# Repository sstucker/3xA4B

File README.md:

# 3xA4B
Utility PCB board. DC summing amplifier. Channels A are divided by 4 and optionally routed through a basic passive filter before being added to Channels B.

Three channels. BNC inputs and outputs. DIN-6 input for +12/-12 DC in. 

Schematic and board available in EAGLE formats. Some parts will need to be substituted. CAM data archive provided as well.

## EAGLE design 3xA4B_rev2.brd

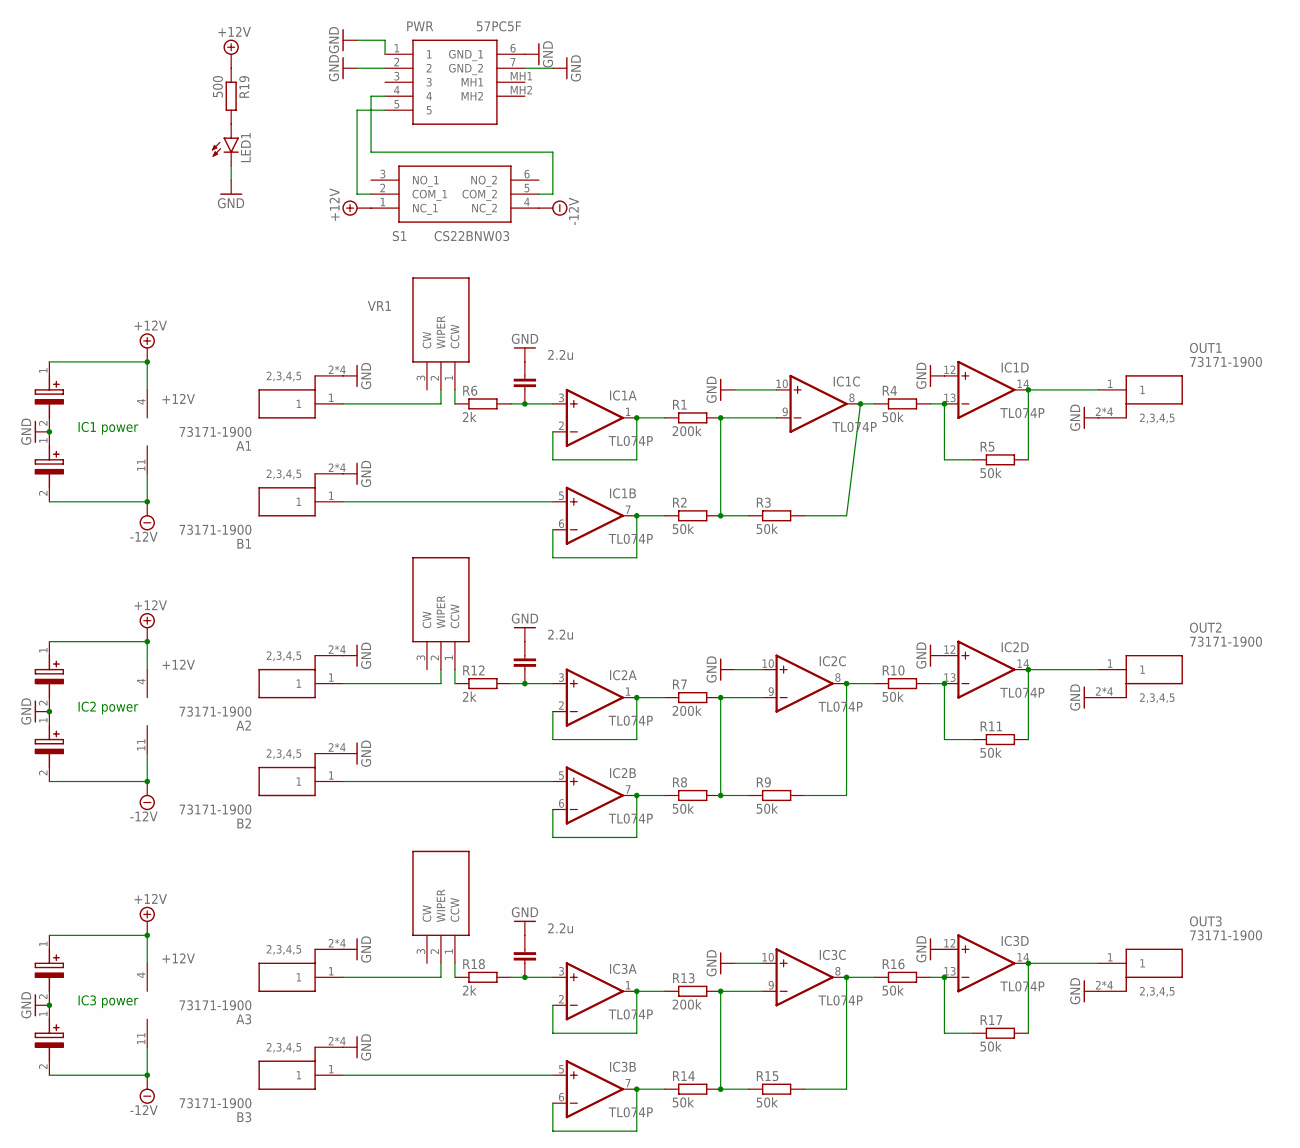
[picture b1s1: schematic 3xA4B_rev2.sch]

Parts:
A1, A2, A3: 73171-1900
B1, B2, B3: 73171-1900
C1, C2, C3, C4, C5, C6: TAP225K050GSB
IC1, IC2, IC3: TL074P; DIL14
LED1: LED3MM
OUT1, OUT2, OUT3: 73171-1900
PWR: 57PC5F; MPN 57PC5F
R1, R7, R13: 200k; 0207/10
R2, R3, R4, R5, R8, R9, R10, R11, R14, R15, R16, R17: 50k; 0207/10
R6, R12, R18: 2k; 0207/10
R19: 500; 0207/10
S1: CS22BNW03; MPN CS22BNW03
VC1, VC2, VC3: 2.2u; C025-024X044
VR1, VR2, VR3: 3299W-1-104LF; 3299W-1-104LF_1; MPN 3299W-1-104LF

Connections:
+12V: C1.1 (+), C3.1 (+), C5.1 (+), IC1.4 (V+), IC2.4 (V+), IC3.4 (V+), R19.1, S1.1 (NC_1)
-12V: C2.2 (-), C4.2 (-), C6.2 (-), IC1.11 (V-), IC2.11 (V-), IC3.11 (V-), S1.4 (NC_2)
GND: A1.2 (2,3,4,5), A1.3 (2,3,4,5), A1.4 (2,3,4,5), A1.5 (2,3,4,5), A2.2 (2,3,4,5), A2.3 (2,3,4,5), A2.4 (2,3,4,5), A2.5 (2,3,4,5), A3.2 (2,3,4,5), A3.3 (2,3,4,5), A3.4 (2,3,4,5), A3.5 (2,3,4,5), B1.2 (2,3,4,5), B1.3 (2,3,4,5), B1.4 (2,3,4,5), B1.5 (2,3,4,5), B2.2 (2,3,4,5), B2.3 (2,3,4,5), B2.4 (2,3,4,5), B2.5 (2,3,4,5), B3.2 (2,3,4,5), B3.3 (2,3,4,5), B3.4 (2,3,4,5), B3.5 (2,3,4,5), C1.2 (-), C2.1 (+), C3.2 (-), C4.1 (+), C5.2 (-), C6.1 (+), IC1.10 (+IN), IC1.12 (+IN), IC2.10 (+IN), IC2.12 (+IN), IC3.10 (+IN), IC3.12 (+IN), LED1.K (C), OUT1.2 (2,3,4,5), OUT1.3 (2,3,4,5), OUT1.4 (2,3,4,5), OUT1.5 (2,3,4,5), OUT2.2 (2,3,4,5), OUT2.3 (2,3,4,5), OUT2.4 (2,3,4,5), OUT2.5 (2,3,4,5), OUT3.2 (2,3,4,5), OUT3.3 (2,3,4,5), OUT3.4 (2,3,4,5), OUT3.5 (2,3,4,5), PWR.1, PWR.2, PWR.6 (GND_1), PWR.7 (GND_2), VC1.1, VC2.1, VC3.1
unnamed: IC1.1 (OUT), IC1.2 (-IN), R1.1
unnamed: IC1.9 (-IN), R1.2, R2.2, R3.1
unnamed: A1.1, VR1.2 (WIPER)
unnamed: IC1.8 (OUT), R3.2, R4.1
unnamed: IC1.13 (-IN), R4.2, R5.1
unnamed: IC1.14 (OUT), OUT1.1, R5.2
unnamed: IC1.3 (+IN), R6.2, VC1.2
unnamed: B1.1, IC1.5 (+IN)
unnamed: IC1.6 (-IN), IC1.7 (OUT), R2.1
unnamed: PWR.5, S1.2 (COM_1)
unnamed: PWR.4, S1.5 (COM_2)
unnamed: LED1.A, R19.2
unnamed: IC2.1 (OUT), IC2.2 (-IN), R7.1
unnamed: IC2.9 (-IN), R7.2, R8.2, R9.1
unnamed: IC2.8 (OUT), R9.2, R10.1
unnamed: IC2.13 (-IN), R10.2, R11.1
unnamed: IC2.14 (OUT), OUT2.1, R11.2
unnamed: IC2.3 (+IN), R12.2, VC2.2
unnamed: B2.1, IC2.5 (+IN)
unnamed: IC2.6 (-IN), IC2.7 (OUT), R8.1
unnamed: A2.1, VR2.2 (WIPER)
unnamed: R12.1, VR2.1 (CCW)
unnamed: IC3.1 (OUT), IC3.2 (-IN), R13.1
unnamed: IC3.9 (-IN), R13.2, R14.2, R15.1
unnamed: IC3.8 (OUT), R15.2, R16.1
unnamed: IC3.13 (-IN), R16.2, R17.1
unnamed: IC3.14 (OUT), OUT3.1, R17.2
unnamed: IC3.3 (+IN), R18.2, VC3.2
unnamed: B3.1, IC3.5 (+IN)
unnamed: IC3.6 (-IN), IC3.7 (OUT), R14.1
unnamed: R6.1, VR1.1 (CCW)
unnamed: A3.1, VR3.2 (WIPER)
unnamed: R18.1, VR3.1 (CCW)

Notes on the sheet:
IC1 power
IC2 power
IC3 power

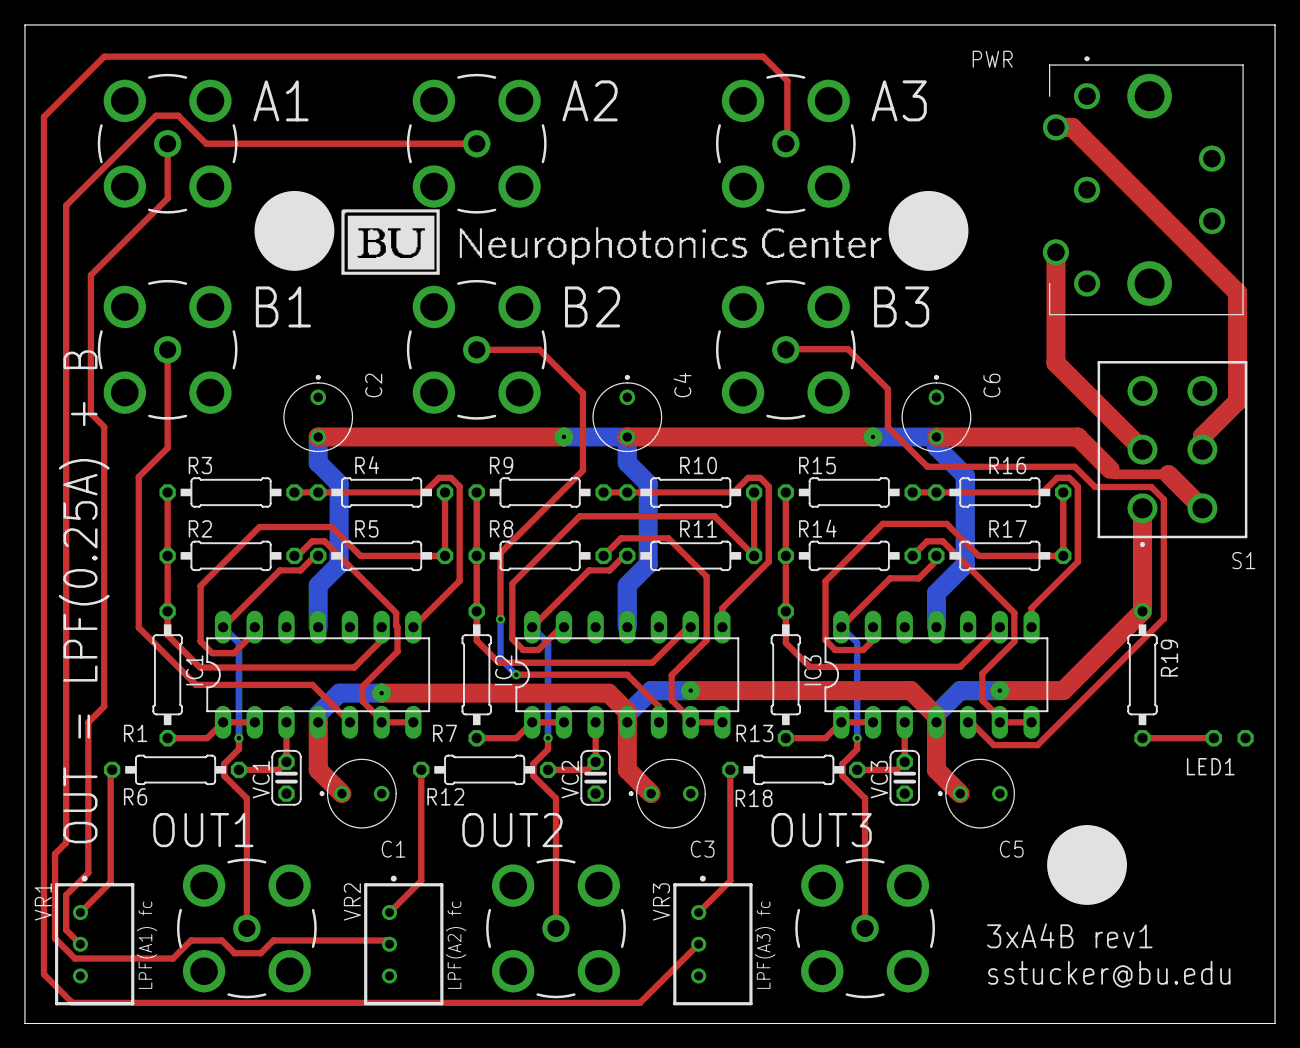
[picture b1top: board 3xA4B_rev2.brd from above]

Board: 2 copper layers, 100.2 x 80.0 mm, 46 parts (1 on the bottom side), 36 nets.

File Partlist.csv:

Partlist
Exported from 3xA4B_rev2.brd at 1/18/2022 18:08
EAGLE Version 9.6.2 Copyright (c) 1988-2020 Autodesk, Inc.

Assembly variant: 

Part     Value          Package         Library        Position (mil)        Orientation

A1       73171-1900     73171-1900      SamacSys_Parts (450 2775)            R0
A2       73171-1900     73171-1900      SamacSys_Parts (1425 2775)           R0
A3       73171-1900     73171-1900      SamacSys_Parts (2400 2775)           R0
B1       73171-1900     73171-1900      SamacSys_Parts (450 2125)            R0
B2       73171-1900     73171-1900      SamacSys_Parts (1425 2125)           R0
B3       73171-1900     73171-1900      SamacSys_Parts (2400 2125)           R0
C1       TAP225K050GSB  TAP225K050GSB   SamacSys_Parts (1000 725)            R0
C2       TAP225K050GSB  TAP225K050GSB   SamacSys_Parts (925 1975)            R270
C3       TAP225K050GSB  TAP225K050GSB   SamacSys_Parts (1975 725)            R0
C4       TAP225K050GSB  TAP225K050GSB   SamacSys_Parts (1900 1975)           R270
C5       TAP225K050GSB  TAP225K050GSB   SamacSys_Parts (2950 725)            R0
C6       TAP225K050GSB  TAP225K050GSB   SamacSys_Parts (2875 1975)           R270
IC1      TL074P         DIL14           linear         (925 1100)            R0
IC2      TL074P         DIL14           linear         (1900 1100)           R0
IC3      TL074P         DIL14           linear         (2875 1100)           R0
LED1                    LED3MM          led            (3800 900)            MR180
OUT1     73171-1900     73171-1900      SamacSys_Parts (700 300)             R0
OUT2     73171-1900     73171-1900      SamacSys_Parts (1675 300)            R0
OUT3     73171-1900     73171-1900      SamacSys_Parts (2650 300)            R0
PWR      57PC5F         57PC5F          SamacSys_Parts (3350 2925)           R180
R1       200k           0207/10         rcl            (450 1100)            R90
R2       50k            0207/10         rcl            (650 1475)            R180
R3       50k            0207/10         rcl            (650 1675)            R0
R4       50k            0207/10         rcl            (1125 1675)           R0
R5       50k            0207/10         rcl            (1125 1475)           R180
R6       2k             0207/10         rcl            (475 800)             R0
R7       200k           0207/10         rcl            (1425 1100)           R90
R8       50k            0207/10         rcl            (1625 1475)           R180
R9       50k            0207/10         rcl            (1625 1675)           R0
R10      50k            0207/10         rcl            (2100 1675)           R0
R11      50k            0207/10         rcl            (2100 1475)           R180
R12      2k             0207/10         rcl            (1450 800)            R0
R13      200k           0207/10         rcl            (2400 1100)           R90
R14      50k            0207/10         rcl            (2600 1475)           R180
R15      50k            0207/10         rcl            (2600 1675)           R0
R16      50k            0207/10         rcl            (3075 1675)           R0
R17      50k            0207/10         rcl            (3075 1475)           R180
R18      2k             0207/10         rcl            (2425 800)            R0
R19      500            0207/10         rcl            (3525 1100)           R270
S1       CS22BNW03      CS22BNW03       SamacSys_Parts (3525 1625)           R0
VC1      2.2u           C025-024X044    rcl            (825 775)             R90
VC2      2.2u           C025-024X044    rcl            (1800 775)            R90
VC3      2.2u           C025-024X044    rcl            (2775 775)            R90
VR1      3299W-1-104LF  3299W-1-104LF_1 SamacSys_Parts (175 250)             R180
VR2      3299W-1-104LF  3299W-1-104LF_1 SamacSys_Parts (1150 250)            R180
VR3      3299W-1-104LF  3299W-1-104LF_1 SamacSys_Parts (2125 250)            R180
